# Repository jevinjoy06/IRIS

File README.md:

# IRIS

**Intelligent Responsive Interface System** — a personal voice assistant with an FPGA wake-word accelerator.

Hub-and-spoke architecture: a GPU desktop runs the hub (brain + memory), and any client device connects over WebSocket to talk to it.

---

## Architecture

```
Desktop PC (hub)
├── FastAPI + WebSocket server  ← brain lives here
├── Ollama LLM (llama3.1:8b)
├── SQLite memory
└── Web UI at http://localhost:7865

Clients (connect over Tailscale)
└── clients/laptop/  ← the IRIS client (orb + voice + text); hub_url set to localhost
    (same machine) or the hub's Tailscale IP (remote device)
```

---

## Quick Start

### 1. Hub (run on your GPU desktop)

```bash
# Install deps
pip install -r hub/requirements.txt

# Configure
cp hub/.env.template hub/.env
# Edit hub/.env — set OLLAMA_BASE_URL and OLLAMA_MODEL
# HUB_HOST defaults to 127.0.0.1 (local only). To let other devices connect,
# set HUB_HOST in hub/.env to this machine's Tailscale IP.
# IMPORTANT: once you do, the hub stops listening on 127.0.0.1 entirely —
# EVERY client's hub_url must point at that same Tailscale IP, including a
# client running on the hub machine itself; "ws://localhost:7865/ws" will no
# longer connect anywhere.

# Run Ollama (separate terminal)
ollama serve
ollama pull llama3.1:8b

# Start the hub
python -m hub
# → http://localhost:7865
```

### 2. Laptop Client

```bash
pip install -r clients/laptop/requirements.txt

# Install Tailscale on the laptop, log into the same account as the desktop
# Then:
cp clients/laptop/config.json.template clients/laptop/config.json
python clients/laptop/main.py
```

### Background agent (optional)

To let IRIS run commands on this device even when the chat window isn't open,
start `python clients/laptop/agent.py` at login:

1. Press `Win+R`, type `shell:startup`, press Enter.
2. Create a shortcut in that folder targeting:
   `pythonw.exe C:\path\to\IRIS\clients\laptop\agent.py`
3. Log out and back in (or just run the script manually) to confirm it connects.

The agent reuses `clients/laptop/config.json` (same `hub_url`/`device_name` as
the chat client) and reconnects automatically if the hub is unreachable or the
connection drops, so it's safe to leave running unattended.

---

## Repo Layout

| Path | What it is |
|---|---|
| `hub/` | FastAPI + WebSocket server, Ollama brain, SQLite memory |
| `clients/laptop/` | The IRIS client — runs on any device, local or remote over Tailscale |
| `clients/hub-dashboard/` | Admin/monitoring app for the hub machine specifically |
| `voice/` | Shared voice pipeline: wake word → VAD → transcription (Moonshine) |
| `hardware/` | Verilog FPGA accelerator (Basys 3, Artix-7 XC7A35T) |
| `docs/` | Design docs |

---

## Networking

Clients connect to the hub over [Tailscale](https://tailscale.com) — a free mesh VPN that gives every device a stable private IP regardless of network. No port forwarding or domain needed.

1. Install Tailscale on all devices
2. Log into the same account
3. Desktop Tailscale IP: `100.74.253.30` (set in `clients/laptop/config.json`)

---

## Hardware (FPGA Accelerator)

Target: **Basys 3** (Artix-7 XC7A35T)

| Phase | What | Status |
|---|---|---|
| 1 | Single MAC unit (`hardware/rtl/mac_unit.v`) | In progress |
| 2 | Systolic array (chained MACs) | Planned |
| 3 | Wake-word neural net on FPGA + audio front-end PCB (KiCad) | Planned |

When the FPGA detects the wake word it sends a UART trigger → voice pipeline takes over.

---

## Voice Pipeline

```
Wake word ("computer") → VAD recording → Moonshine transcription → hub WebSocket → Ollama → response
```

Set `KERAS_BACKEND=torch` before running (avoids a TensorFlow install).

Custom wake word via Picovoice Porcupine — add your `.ppn` file to `voice/` when trained.

---

## Secrets

Never commit: `hub/.env`, `voice/config.json`, `clients/*/config.json`

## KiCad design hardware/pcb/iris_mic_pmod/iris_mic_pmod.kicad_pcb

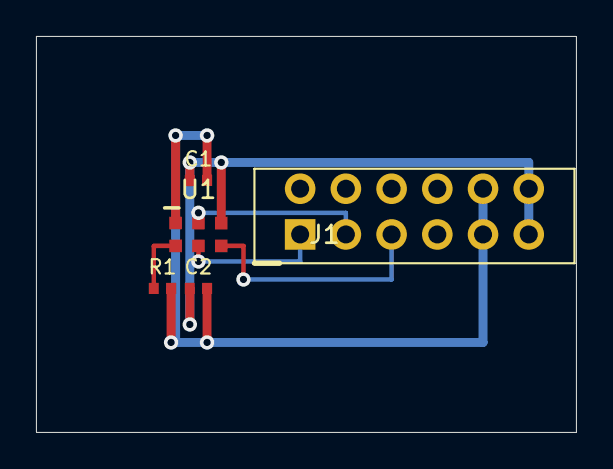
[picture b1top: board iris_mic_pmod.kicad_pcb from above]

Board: 2 copper layers, 30.0 x 22.0 mm, 5 parts (0 on the bottom side), 6 nets.

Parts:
C1: 100nF; C_0402_1005Metric
C2: 10uF; C_0402_1005Metric
J1: PMOD_2x6; PinHeader_2x06_P2.54mm_Vertical
R1: 0R; R_0402_1005Metric
U1: SPH0645LM4H

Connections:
+3V3: C1.1, C2.1, J1.11, J1.12, U1.3
GND: C1.2, C2.2, J1.9, J1.10, R1.2, U1.1
I2S_CLK: J1.3, U1.2
I2S_DATA: J1.1, U1.5
I2S_WS: J1.5, U1.6
L_R: R1.1, U1.4

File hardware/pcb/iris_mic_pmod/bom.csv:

Reference,Value,Footprint,Quantity
R1,0R,Resistor_SMD,1
C1,100nF,Capacitor_SMD,1
C2,10uF,Capacitor_SMD,1
J1,PMOD_2x6,Connector_PinHeader_2.54mm,1
U1,SPH0645LM4H,Microphone,1
